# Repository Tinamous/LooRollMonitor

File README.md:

Toilet Roll Monitor
===================

Never run out of toilet paper again!

Internet collected toilet roll pole, constructed of a 3D printed base and a acrylic tube (pole) which the toilet paper rolls are stacked, internet connected with a Particle.io Photon.

The presense of toilet rolls are sensed with a IR reflectance sensor. Reflected IR signal == roll preset, no reflection == no roll.

Uses Photon with WiFi connection which is high power and 20mA drive for 3x IR LEDs, however the Photon can be put in low power mode (no WiFi)
and roll sensing only needs to be done occasionally.

## Why:
* Why not ;-)
* Guest bathrooms you don't check all that often - get notification on low toilet paper before your guess runs out.
* Day to day automation, never forget to order toilet paper again.

### Design issues:

#### V1: 
* Somewhat high power using photon and WiFi, most likely batteries will runout before toilet paper!
* Multiboard design clumsy to solder together but flexible from 1 to 4 roll sensors
* limited connections means all leds are driven at once (@20mA), so 3 roll system sees 60mA spike
* PCB mounted AA battery holders were just a bit too big to fit in the acrylic tube so batteries embedded in the 3D printed base.
* Humidity/temperature sensor, maybe not so useful? Difficult to solder on.

### V2 Options:
* Replace Photon with Bluz (or Zigbee + SmartThings combo).
* Single board to allow better signal routing and less soldering of connections.
* Possible to use PCB mounted coin cells if Bluz low power enough 
* Use through hole version of sensor for easier soldering

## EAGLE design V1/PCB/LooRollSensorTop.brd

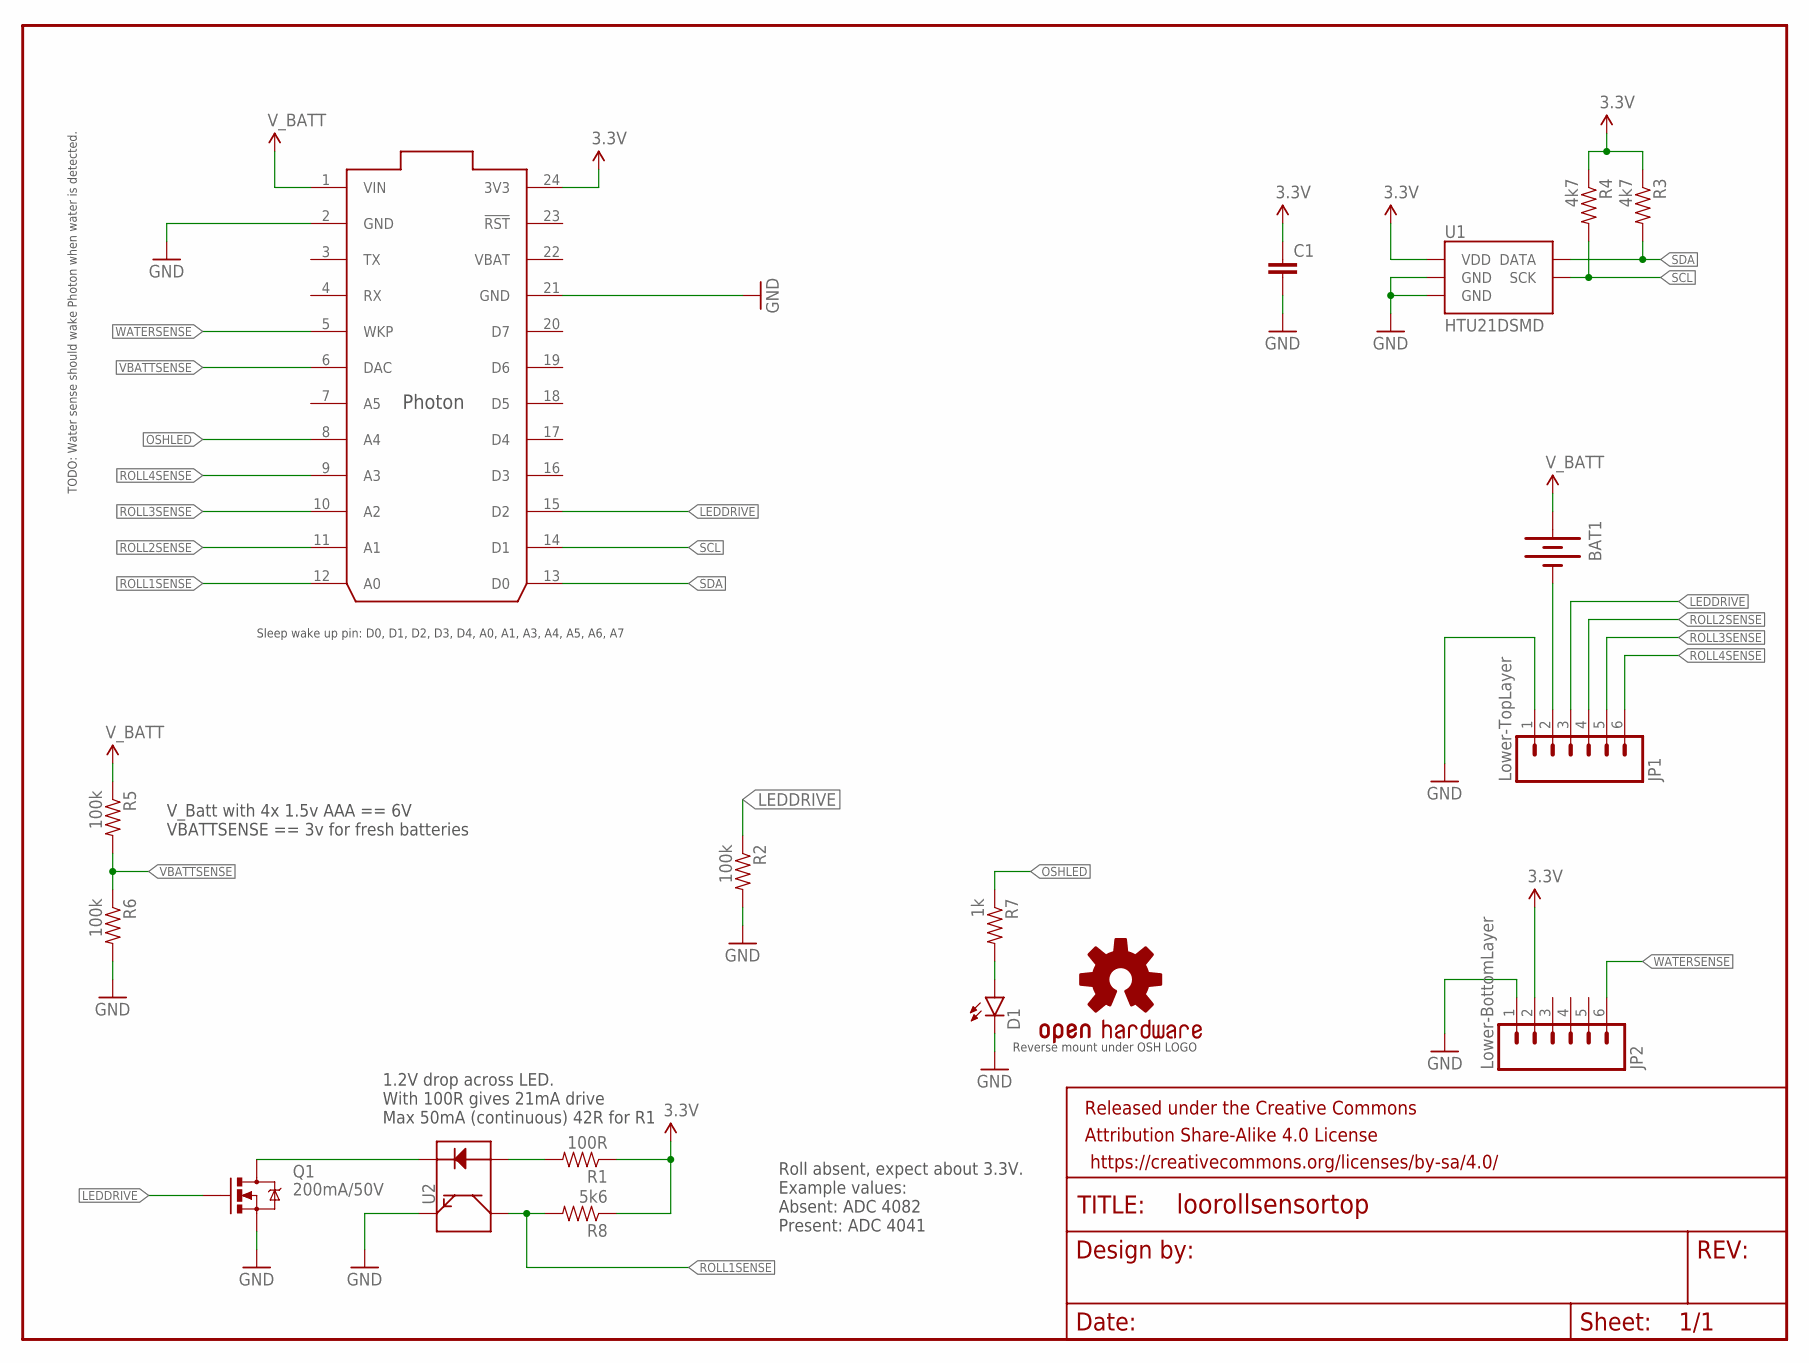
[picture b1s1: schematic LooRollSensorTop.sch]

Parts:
BAT1: BATTERYAA-PANEL; BATTERY-AA-PANEL; FARNELL 1650669
C1: CAP0805; 0805
D1: LED1206-BOTTOM; LED-1206-BOTTOM
FRAME1: FRAME-LETTER; CREATIVE_COMMONS
JP1: Lower-TopLayer; 1X06-SMD_EDGE
JP2: Lower-BottomLayer; 1X06-SMD_EDGE
LOGO1: OSHW-LOGOM; OSHW-LOGO-M
Q1: 200mA/50V; SOT23-3
R1: 100R; 1206
R2, R5, R6: 100k; 1206
R3, R4: 4k7; 1206
R7: 1k; 1206
R8: 5k6; 1206
U1: HTU21DSMD; HTU21D
U2: QRE1113SMD-W; QRE1113-W
U$1: PHOTON_WITH_HEADERS; PHOTON

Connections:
3.3V: C1.1, JP2.2, R1.1, R3.1, R4.1, R8.1, U1.VDD, U$1.24 (3V3)
GND: C1.2, D1.C, JP1.1, JP2.1, Q1.2 (S), R2.2, R6.2, U1.7 (GND), U1.GND, U2.4 (E), U$1.2 (GND), U$1.21 (GND)
LEDDRIVE: JP1.3, Q1.1 (G), R2.1, U$1.15 (D2)
unnamed: Q1.3 (D), U2.2 (K)
unnamed: R1.2, U2.1 (A)
unnamed: D1.A, R7.2
unnamed: BAT1.-, JP1.2
OSHLED: R7.1, U$1.8 (A4)
ROLL1SENSE: R8.2, U2.3 (C), U$1.12 (A0)
ROLL2SENSE: JP1.4, U$1.11 (A1)
ROLL3SENSE: JP1.5, U$1.10 (A2)
ROLL4SENSE: JP1.6, U$1.9 (A3)
SCL: R4.2, U1.SCK, U$1.14 (D1)
SDA: R3.2, U1.DATA, U$1.13 (D0)
VBAT: U$1.22 (VBAT)
VBATTSENSE: R5.2, R6.1, U$1.6 (DAC)
V_BATT: BAT1.+, R5.1, U$1.1 (VIN)
WATERSENSE: JP2.6, U$1.5 (WKP)

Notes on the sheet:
Sleep wake up pin: D0, D1, D2, D3, D4, A0, A1, A3, A4, A5, A6, A7
TODO: Water sense should wake Photon when water is detected.
Reverse mount under OSH LOGO
1.2V drop across LED. With 100R gives 21mA drive Max 50mA (continuous) 42R for R1
Roll absent, expect about 3.3V. Example values: Absent: ADC 4082 Present: ADC 4041
V_Batt with 4x 1.5v AAA == 6V VBATTSENSE == 3v for fresh batteries

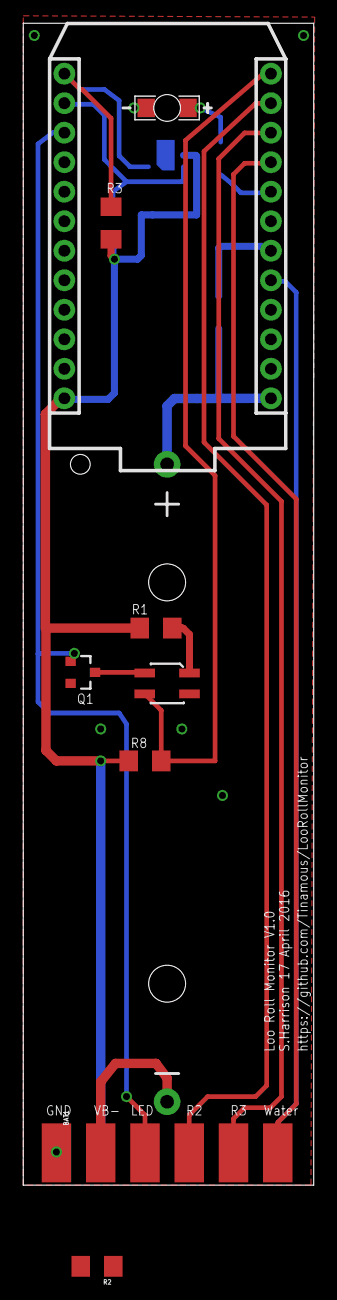
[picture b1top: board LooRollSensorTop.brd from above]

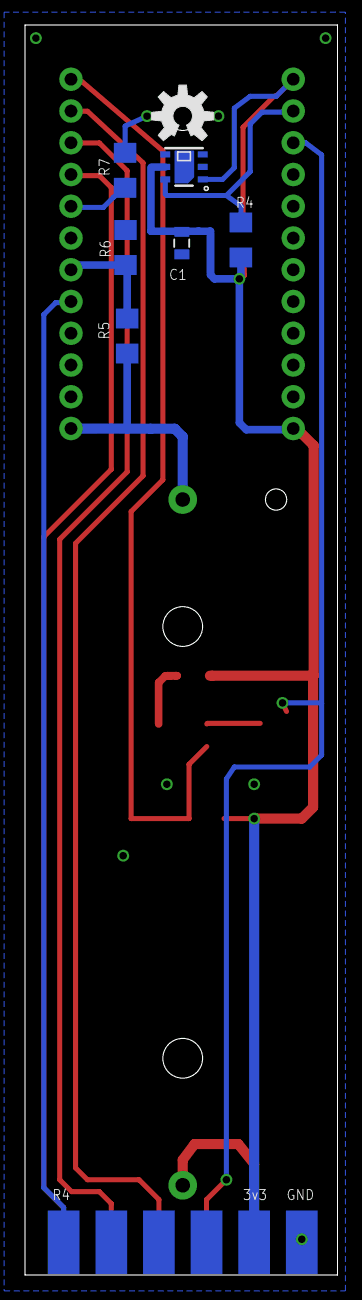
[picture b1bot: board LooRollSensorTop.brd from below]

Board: 2 copper layers, 25.0 x 100.0 mm, 19 parts (8 on the bottom side), 17 nets.

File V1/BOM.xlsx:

R1 | 100R | 1206
R2
R3 | 4k7 | 1206
R4 | 4k7 | 1206
R5 | 100k | 1206
R6 | 100k | 1206
R7 | 1k | 1206
C1 | 0.1uF | 805
U1 | HTU21D
D1 | LED | 1206 Reverse

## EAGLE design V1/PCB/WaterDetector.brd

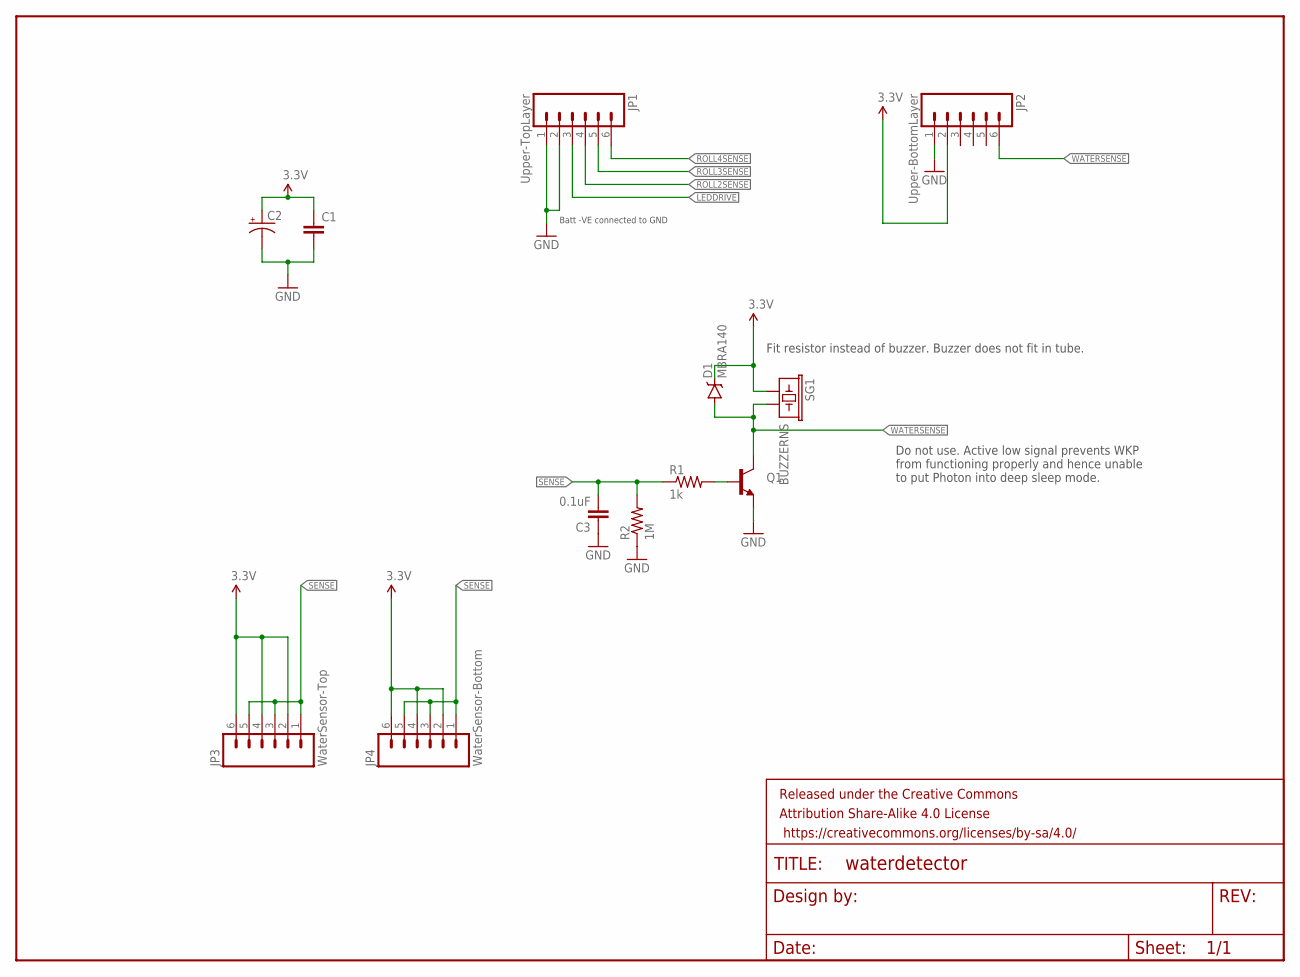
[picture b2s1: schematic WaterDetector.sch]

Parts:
C1: CAP0805; 0805
C2: CAP_POLC; PANASONIC_C
C3: 0.1uF; 0805
D1: MBRA140; SMA-DIODE
FRAME1: FRAME-LETTER; CREATIVE_COMMONS
JP1: Upper-TopLayer; 1X06-SMD_EDGE
JP2: Upper-BottomLayer; 1X06-SMD_EDGE
JP3: WaterSensor-Top; 1X06-SMD_EDGE
JP4: WaterSensor-Bottom; 1X06-SMD_EDGE
Q1: TRANSISTOR_NPNSOT23-3; SOT23-3
R1: 1k; 1206
R2: 1M; 1206
SG1: BUZZERNS; BUZZER-12MM-NS

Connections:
3.3V: C1.1, C2.+, D1.C, JP2.2, JP3.2, JP3.4, JP3.6, JP4.2, JP4.4, JP4.6, SG1.+ (1)
GND: C1.2, C2.-, C3.1, JP1.1, JP1.2, JP2.1, Q1.2 (E), R2.1
LEDDRIVE: JP1.3
unnamed: Q1.1 (B), R1.2
ROLL2SENSE: JP1.4
ROLL3SENSE: JP1.5
ROLL4SENSE: JP1.6
SENSE: C3.2, JP3.1, JP3.3, JP3.5, JP4.1, JP4.3, JP4.5, R1.1, R2.2
WATERSENSE: D1.A, JP2.6, Q1.3 (C), SG1.- (2)

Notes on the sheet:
Batt -VE connected to GND
Do not use. Active low signal prevents WKP from functioning properly and hence unable to put Photon into deep sleep mode.
Fit resistor instead of buzzer. Buzzer does not fit in tube.

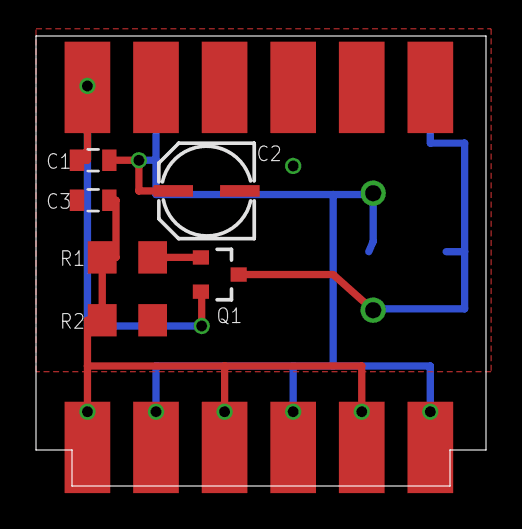
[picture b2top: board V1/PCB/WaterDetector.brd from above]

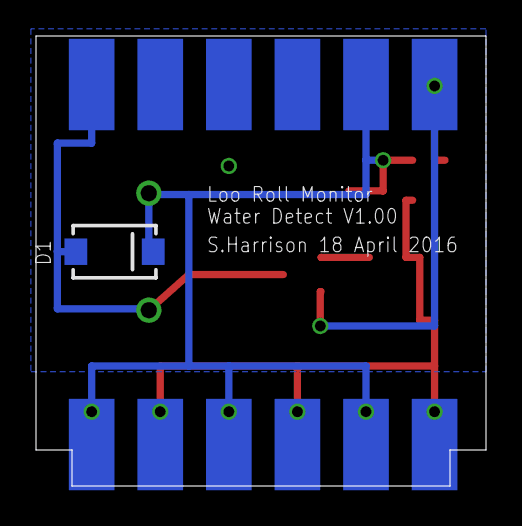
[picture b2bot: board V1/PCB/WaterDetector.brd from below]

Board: 2 copper layers, 25.0 x 25.0 mm, 13 parts (3 on the bottom side), 5 nets.

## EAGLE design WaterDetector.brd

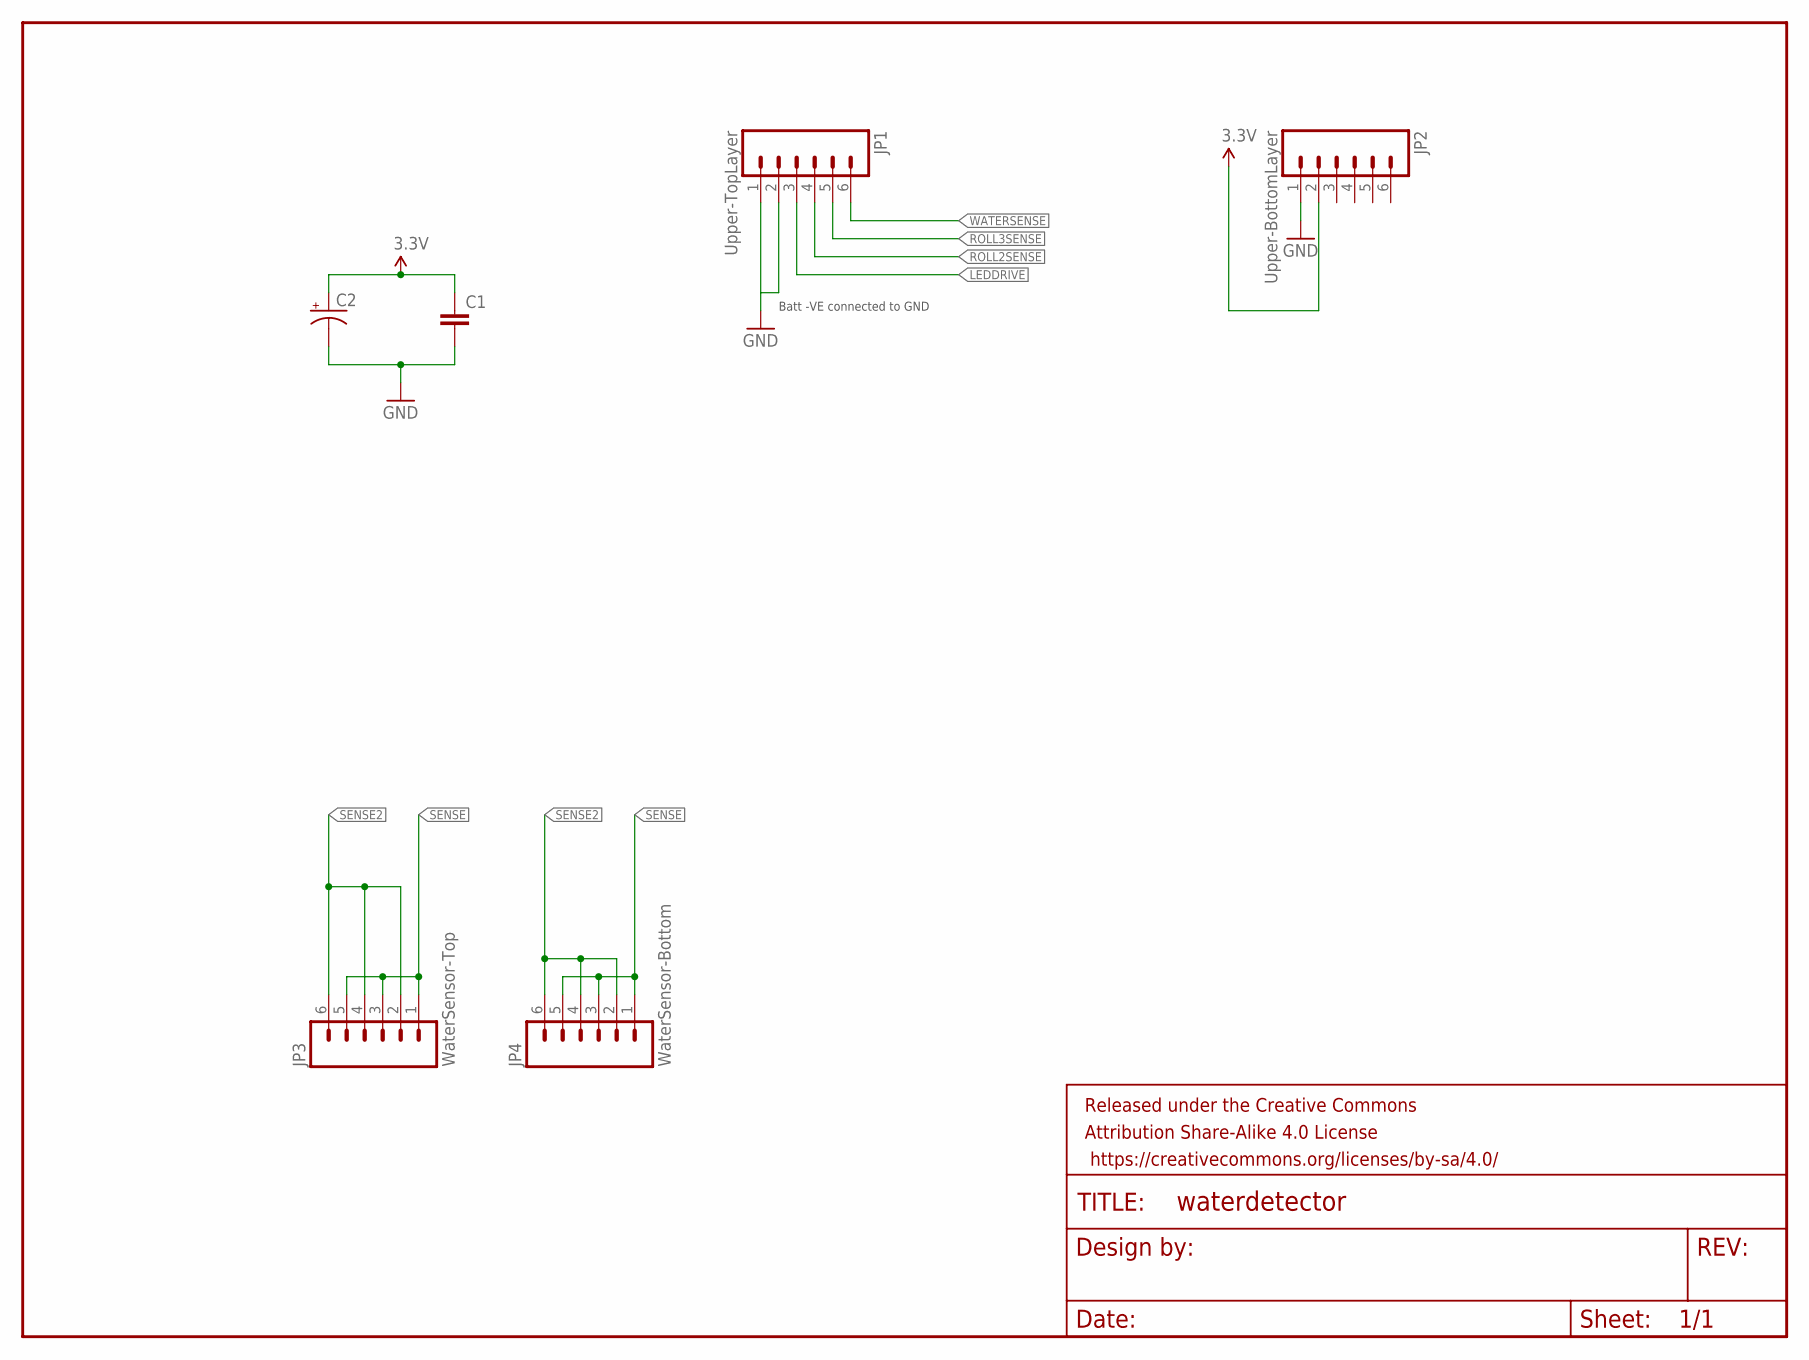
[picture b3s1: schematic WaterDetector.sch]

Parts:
C1: CAP0805; 0805
C2: CAP_POLC; PANASONIC_C
FRAME1: FRAME-LETTER; CREATIVE_COMMONS
JP1: Upper-TopLayer; 1X06-SMD_EDGE
JP2: Upper-BottomLayer; 1X06-SMD_EDGE
JP3: WaterSensor-Top; 1X06-SMD_EDGE
JP4: WaterSensor-Bottom; 1X06-SMD_EDGE

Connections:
3.3V: C1.1, C2.+, JP2.2
GND: C1.2, C2.-, JP1.1, JP1.2, JP2.1
LEDDRIVE: JP1.3
ROLL2SENSE: JP1.4
ROLL3SENSE: JP1.5
SENSE: JP3.1, JP3.3, JP3.5, JP4.1, JP4.3, JP4.5
SENSE2: JP3.2, JP3.4, JP3.6, JP4.2, JP4.4, JP4.6
WATERSENSE: JP1.6

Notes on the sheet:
Batt -VE connected to GND

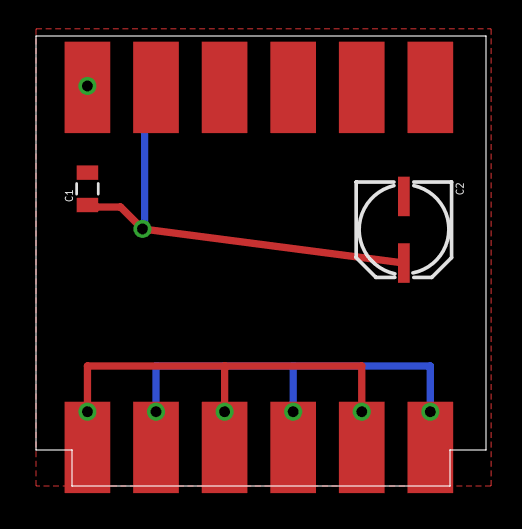
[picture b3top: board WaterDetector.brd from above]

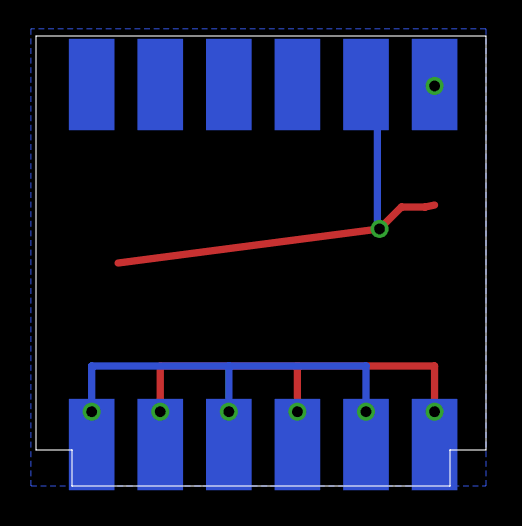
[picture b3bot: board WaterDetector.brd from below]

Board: 2 copper layers, 25.0 x 25.0 mm, 7 parts (2 on the bottom side), 4 nets.

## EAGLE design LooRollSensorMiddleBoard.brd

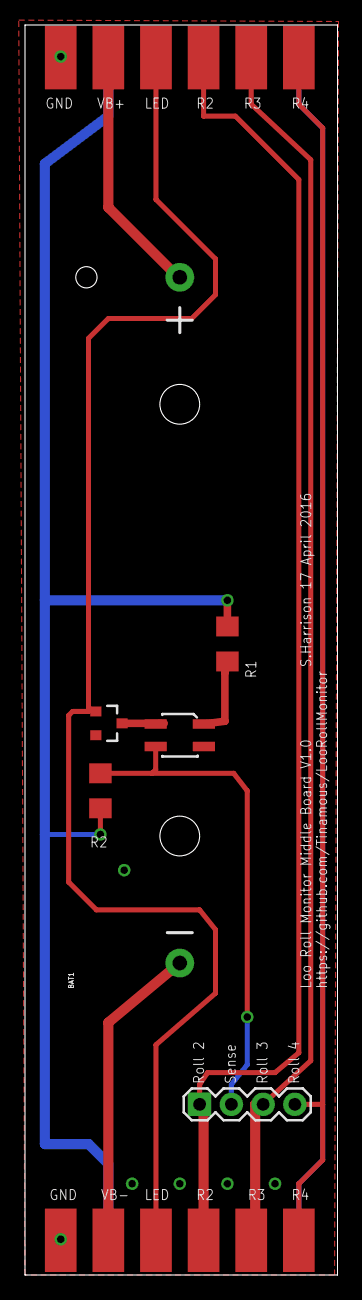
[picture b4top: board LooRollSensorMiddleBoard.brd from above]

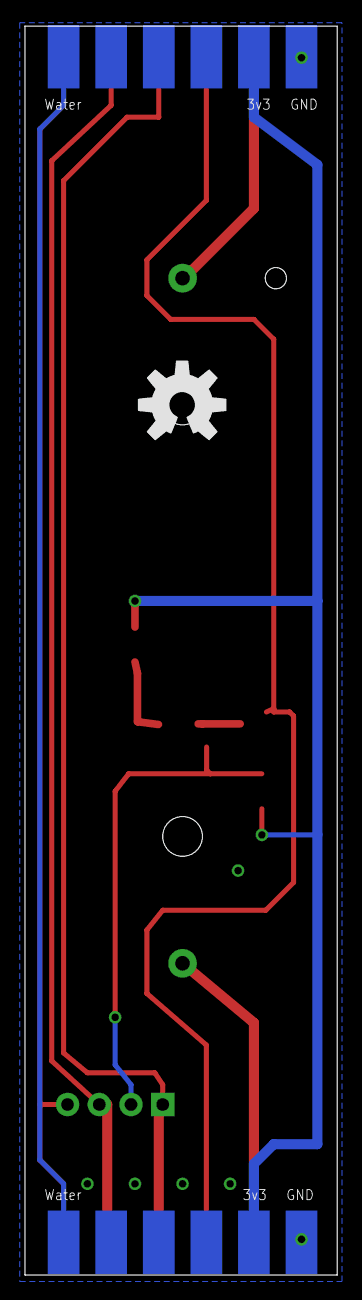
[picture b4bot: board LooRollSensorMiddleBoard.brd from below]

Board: 2 copper layers, 25.0 x 100.0 mm, 12 parts (3 on the bottom side), 12 nets.

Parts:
BAT1: BATTERY-AA-PANEL
FRAME1: FRAME-LEDGER; CREATIVE_COMMONS
JP1: Upper-TopLayer; 1X06-SMD_EDGE
JP2: Lower-TopLayer; 1X06-SMD_EDGE
JP3: RollSelector; 1X04
JP4: Lower-BottomLayer; 1X06-SMD_EDGE
JP5: Upper-BottomLayer; 1X06-SMD_EDGE
LOGO1: OSHW-LOGOL; OSHW-LOGO-L
Q1: 200mA/50V; SOT23-3
R1: 100R; 1206
R2: 5k6; 1206
U1: QRE1113-W

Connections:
3.3V: JP4.2, JP5.2, R1.1, R2.1
BATT+VE: BAT1.+, JP1.2
BATT-VE: BAT1.-, JP2.2
GND: JP1.1, JP2.1, JP4.1, JP5.1, Q1.2, U1.4
LEDDRIVE: JP1.3, JP2.3, Q1.1
unnamed: Q1.3, U1.2
unnamed: R1.2, U1.1
ROLL2SENSE: JP1.4, JP2.4, JP3.1
ROLL3SENSE: JP1.5, JP2.5, JP3.3
ROLL4SENSE: JP1.6, JP2.6, JP3.4
ROLL_SENSE: JP3.2, R2.2, U1.3
WATERSENSE: JP4.6, JP5.6

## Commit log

2016-04-18 Top and middle boards as sent to DirtyPcbs
2016-04-18 Work in progress water detect bottom board
2016-04-18 Added V1 pdf's as sent to DirtyPcbs for fabrication.
2016-04-18 Water detect board V1.00 as sent to DirtyPCBs
2016-08-23 Moved PCB files to a dedicated folder.
2016-08-23 Added 3D printer files to make the base and the top.
2016-08-23 Added QRE1113 datasheet.
2016-08-23 Work in progress firmware. Basics in, calibration working. Water sense not.
2016-08-23 Added work in progress BOM and the .gitignore file.
2016-08-23 Added start of readme
2016-08-23 Minor readme updates.
2016-08-23 More markup improvements to the readme.
2016-08-23 Fixed water sense as it's active low. Added publishing on water sense cleared.
    Set Photon LED to be red if low roll count or water sensed.
    Decreased time before debug mode is existed to 60 seconds, although this might be a bit short.
    Modified debug sleep to monitor water sense rather than a solid 10s sleep.
2016-08-24 Changed field name for WaterSensed as it's not an ADC value.
    Implemented send state (roll count etc) measurements on every wake loop.
2016-08-27 Update to ensure calibration does not happen at the same time as other checking functions.
    Increased initial debug timeout before power saving kicks in.
    Added sensor ADC values to status publishing to help watch for anomolies.
    Modified reasSensor to remove background IR and to have longer delays for reading and between reading IR reflectance levels.
2016-08-27 Added missing junctions
2016-08-28 Removed VBattAdcThreshold in favour of a direct voltage threshold which is easier to understand.
    Added iSCritical to publishStatus so that a delay can be added to the publishing to ensure the message has gone (pending Photon firmware update that includes confirmation).
    Added flag to publishStatus to indicate if a published message may be waiting to allow the deep sleep to be delayed so the messages can be published by the photon.
    Stopped roll monitoring and publishing when the battery level is low to slow down draining the batteries which can be bad for them.
2016-08-30 Added bodge resistor required to pull LED drive low to prevent LEDs switching on when Photon is in power save mode.
    "Printed" eagle files as pdfs.
2016-08-30 Added use of retained variables to keep values in memory when in deep power mode.
    Adde monitoring of time to connect to the cloud and time from wake to sleep.
    Added ability to pusblish calibration values on demand.

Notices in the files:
parts and their libraries:
SparkFun-Sensors: Licensing: Creative Commons ShareAlike 4.0 International - https://creativecommons.org/licenses/by-sa/4.0
SparkFun-Aesthetics: Released under the Creative Commons Attribution Share-Alike 4.0 License
SparkFun-Aesthetics: https://creativecommons.org/licenses/by-sa/4.0
